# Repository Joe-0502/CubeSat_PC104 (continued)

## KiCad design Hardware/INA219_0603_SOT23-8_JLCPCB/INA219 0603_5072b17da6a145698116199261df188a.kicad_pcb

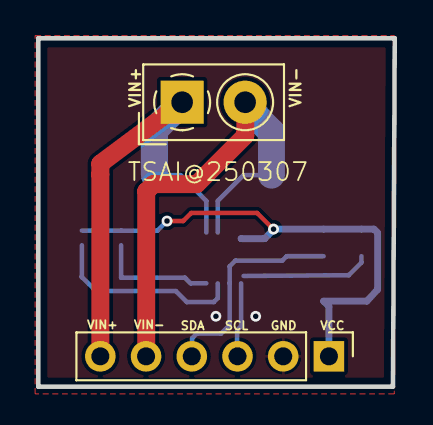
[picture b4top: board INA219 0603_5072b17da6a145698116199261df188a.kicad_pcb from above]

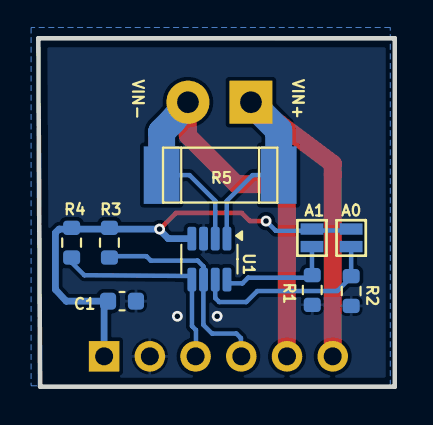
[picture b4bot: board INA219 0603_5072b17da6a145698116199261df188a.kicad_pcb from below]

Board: 2 copper layers, 19.8 x 19.4 mm, 11 parts (9 on the bottom side), 8 nets.

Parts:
C1: 100nF; C_0603_1608Metric
J1: Conn_01x06; PinHeader_1x06_P2.54mm_Vertical
JP1: M023.5MM; TerminalBlock_4Ucon_1x02_P3.50mm_Horizontal_small
R1, R2, R3, R4: 10K; R_0603_1608Metric
R5: 0.1; R_2512
SJ1, SJ2: SOLDERJUMPERNC_TR; SolderJumper_2
U1: INA219AIDCNR; SOT-23-8

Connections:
GND: C1.1, J1.2, R1.2, R2.2, U1.3 (GND)
unnamed: R2.1, SJ2.1, U1.7 (A0)
unnamed: R1.1, SJ1.1, U1.8 (A1)
SCL: J1.3, R4.1, U1.5 (SCL)
SDA: J1.4, R3.1, U1.6 (SDA)
VCC: C1.2, J1.1, R3.2, R4.2, SJ1.2, SJ2.2, U1.4 (VS)
VIN+: J1.6, JP1.1, R5.1, U1.1 (IN+)
VIN-: J1.5, JP1.2, R5.2, U1.2 (IN-)

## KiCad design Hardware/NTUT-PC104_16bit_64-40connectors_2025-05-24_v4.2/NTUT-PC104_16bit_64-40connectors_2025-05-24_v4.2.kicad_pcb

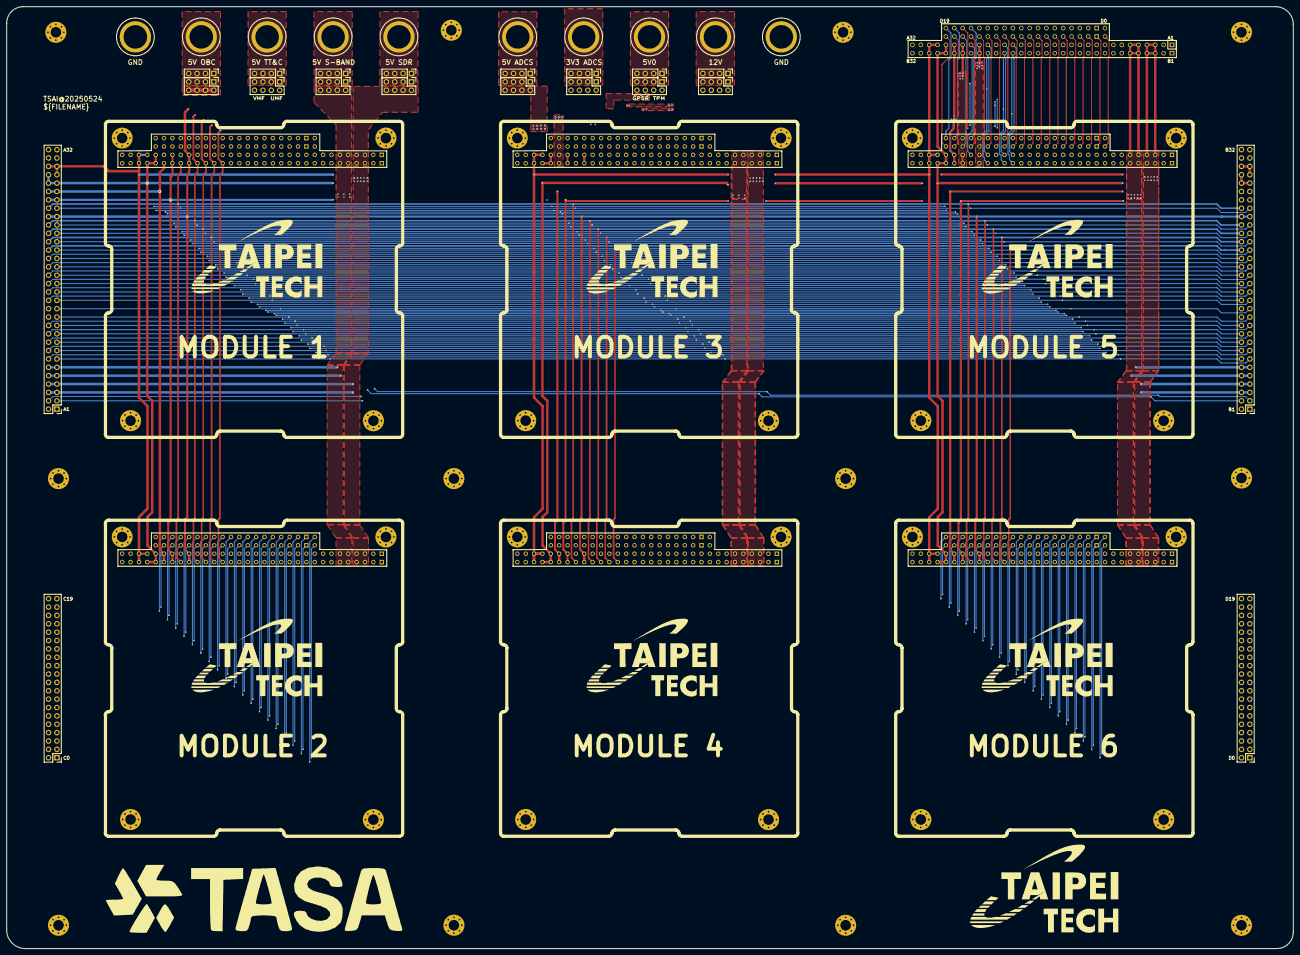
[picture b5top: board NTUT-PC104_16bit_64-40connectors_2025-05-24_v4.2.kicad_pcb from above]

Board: 4 copper layers, 390.3 x 285.7 mm, 49 parts (0 on the bottom side), 92 nets.

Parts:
H1, H2, H3, H4, H5, H6, H7, H8, H9, H10, H11, H12: MountingHole_Pad; MountingHole_3.2mm_M3_Pad_Via
J1, J2, J3, J4, J5, J6: CubeSat_PC104_16bit_footprint
J7, J12, J13, J14, J15, J16, J17, J18: Conn_02x04_Odd_Even; PinHeader_2x04_P2.54mm_Vertical
J8, J10: Conn_02x26_Odd_Even; PinHeader_2x20_P2.54mm_Vertical
J9: Conn_02x26_Odd_Even; PinHeader_2x32_P2.54mm_Vertical
J11: PC104_16bit_Connector
J19, J20, J21, J22, J23, J24, J25, J26: Conn_01x04; PinHeader_1x04_P2.54mm_Vertical
JA19: Conn_02x26_Odd_Even; PinHeader_2x32_P2.54mm_Vertical
TP1, TP2, TP3, TP4, TP5, TP6, TP7, TP8, TP9, TP10: TestPoint_Alt; KSE_PN6095

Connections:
/3.3V_ADCS_1W: J1.B22, J2.B22, J3.B22, J4.B22, J5.B22, J6.B22, J9.44, J11.B22, J16.2, J16.4, J16.6, J16.8, JA19.44
/3V3_ADCS: J16.1, J16.3, J16.5, J16.7, J24.1, J24.2, J24.3, J24.4, TP7.1
/5V: J18.1, J18.3, J18.5, J18.7, J26.1, J26.2, J26.3, J26.4, TP9.1
/5V_ADCS: J15.1, J15.3, J15.5, J15.7, J23.1, J23.2, J23.3, J23.4, TP6.1
/5V_ADCS_1.2W: J1.B23, J2.B23, J3.B23, J4.B23, J5.B23, J6.B23, J9.46, J11.B23, J15.2, J15.4, J15.6, J15.8, JA19.46
/5V_GPSR_0.6W: J1.B21, J2.B21, J3.B21, J4.B21, J5.B21, J6.B21, J9.42, J11.B21, J18.6, J18.8, JA19.42
/5V_OBC: J14.1, J14.3, J14.5, J14.7, J22.1, J22.2, J22.3, J22.4, TP4.1
/5V_OBC_5W: J1.A27, J1.B27, J2.A27, J2.B27, J3.A27, J3.B27, J4.A27, J4.B27, J5.A27, J5.B27, J6.A27, J6.B27, J9.53, J9.54, J11.A27, J11.B27, J14.2, J14.4, J14.6, J14.8, JA19.53, JA19.54
/5V_S-BAND: J12.1, J12.3, J12.5, J12.7, J20.1, J20.2, J20.3, J20.4, TP2.1
/5V_S-BAND_12W: J1.A5, J1.A6, J1.B5, J1.B6, J2.A5, J2.A6, J2.B5, J2.B6, J3.A5, J3.A6, J3.B5, J3.B6, J4.A5, J4.A6, J4.B5, J4.B6, J5.A5, J5.A6, J5.B5, J5.B6, J6.A5, J6.A6, J6.B5, J6.B6, J9.9, J9.10, J9.11, J9.12, J11.A5, J11.A6, J11.B5, J11.B6, J12.2, J12.4, J12.6, J12.8, JA19.9, JA19.10, JA19.11, JA19.12
/5V_SDR: J7.1, J7.3, J7.5, J7.7, J19.1, J19.2, J19.3, J19.4, TP1.1
/5V_SDR_10W: J1.A3, J1.A4, J1.B3, J1.B4, J2.A3, J2.A4, J2.B3, J2.B4, J3.A3, J3.A4, J3.B3, J3.B4, J4.A3, J4.A4, J4.B3, J4.B4, J5.A3, J5.A4, J5.B3, J5.B4, J6.A3, J6.A4, J6.B3, J6.B4, J7.2, J7.4, J7.6, J7.8, J9.5, J9.6, J9.7, J9.8, J11.A3, J11.A4, J11.B3, J11.B4, JA19.5, JA19.6, JA19.7, JA19.8
/5V_TPM_0.4W: J1.B20, J2.B20, J3.B20, J4.B20, J5.B20, J6.B20, J9.40, J11.B20, J18.2, J18.4, JA19.40
/5V_TT&C: J13.1, J13.3, J13.5, J13.7, J21.1, J21.2, J21.3, J21.4, TP3.1
/5V_TT&C(UHF)_3.5W: J1.A24, J1.B24, J2.A24, J2.B24, J3.A24, J3.B24, J4.A24, J4.B24, J5.A24, J5.B24, J6.A24, J6.B24, J9.47, J9.48, J11.A24, J11.B24, J13.2, J13.4, JA19.47, JA19.48
/5V_TT&C(VHF)_3.5W: J1.A26, J1.B26, J2.A26, J2.B26, J3.A26, J3.B26, J4.A26, J4.B26, J5.A26, J5.B26, J6.A26, J6.B26, J9.51, J9.52, J11.A26, J11.B26, J13.6, J13.8, JA19.51, JA19.52
/12V: J17.1, J17.3, J17.5, J17.7, J25.1, J25.2, J25.3, J25.4, TP8.1
/+5V: J1.B25, J2.B25, J3.B25, J4.B25, J5.B25, J6.B25, J9.50, J11.B25, JA19.50
/ADSBRX: J1.A23, J2.A23, J3.A23, J4.A23, J5.A23, J6.A23, J9.45, J11.A23, JA19.45
/ADSBTX: J1.A22, J2.A22, J3.A22, J4.A22, J5.A22, J6.A22, J9.43, J11.A22, JA19.43
/BAT_I_AD: J1.B8, J2.B8, J3.B8, J4.B8, J5.B8, J6.B8, J9.16, J11.B8, JA19.16
/C0: J1.C0, J2.C0, J3.C0, J4.C0, J5.C0, J6.C0, J8.1, J10.1, J11.C0
/C1: J1.C1, J2.C1, J3.C1, J4.C1, J5.C1, J6.C1, J8.3, J10.3, J11.C1
/C2: J1.C2, J2.C2, J3.C2, J4.C2, J5.C2, J6.C2, J8.5, J10.5, J11.C2
/C3: J1.C3, J2.C3, J3.C3, J4.C3, J5.C3, J6.C3, J8.7, J10.7, J11.C3
/C4: J1.C4, J2.C4, J3.C4, J4.C4, J5.C4, J6.C4, J8.9, J10.9, J11.C4
/C5: J1.C5, J2.C5, J3.C5, J4.C5, J5.C5, J6.C5, J8.11, J10.11, J11.C5
/C6: J1.C6, J2.C6, J3.C6, J4.C6, J5.C6, J6.C6, J8.13, J10.13, J11.C6
/C7: J1.C7, J2.C7, J3.C7, J4.C7, J5.C7, J6.C7, J8.15, J10.15, J11.C7
/C8: J1.C8, J2.C8, J3.C8, J4.C8, J5.C8, J6.C8, J8.17, J10.17, J11.C8
/C9: J1.C9, J2.C9, J3.C9, J4.C9, J5.C9, J6.C9, J8.19, J10.19, J11.C9
/C10: J1.C10, J2.C10, J3.C10, J4.C10, J5.C10, J6.C10, J8.21, J10.21, J11.C10
/C11: J1.C11, J2.C11, J3.C11, J4.C11, J5.C11, J6.C11, J8.23, J10.23, J11.C11
/C12: J1.C12, J2.C12, J3.C12, J4.C12, J5.C12, J6.C12, J8.25, J10.25, J11.C12
/C13: J1.C13, J2.C13, J3.C13, J4.C13, J5.C13, J6.C13, J8.27, J10.27, J11.C13
/C14: J1.C14, J2.C14, J3.C14, J4.C14, J5.C14, J6.C14, J8.29, J10.29, J11.C14
/C15: J1.C15, J2.C15, J3.C15, J4.C15, J5.C15, J6.C15, J8.31, J10.31, J11.C15
/C16: J1.C16, J2.C16, J3.C16, J4.C16, J5.C16, J6.C16, J8.33, J10.33, J11.C16
/C17: J1.C17, J2.C17, J3.C17, J4.C17, J5.C17, J6.C17, J8.35, J10.35, J11.C17
/C18: J1.C18, J2.C18, J3.C18, J4.C18, J5.C18, J6.C18, J8.37, J10.37, J11.C18
/C19: J1.C19, J2.C19, J3.C19, J4.C19, J5.C19, J6.C19, J8.39, J10.39, J11.C19
/D0: J1.D0, J2.D0, J3.D0, J4.D0, J5.D0, J6.D0, J8.2, J10.2, J11.D0
/D1: J1.D1, J2.D1, J3.D1, J4.D1, J5.D1, J6.D1, J8.4, J10.4, J11.D1
/D2: J1.D2, J2.D2, J3.D2, J4.D2, J5.D2, J6.D2, J8.6, J10.6, J11.D2
/D3: J1.D3, J2.D3, J3.D3, J4.D3, J5.D3, J6.D3, J8.8, J10.8, J11.D3
/D4: J1.D4, J2.D4, J3.D4, J4.D4, J5.D4, J6.D4, J8.10, J10.10, J11.D4
/D5: J1.D5, J2.D5, J3.D5, J4.D5, J5.D5, J6.D5, J8.12, J10.12, J11.D5
/D6: J1.D6, J2.D6, J3.D6, J4.D6, J5.D6, J6.D6, J8.14, J10.14, J11.D6
/D7: J1.D7, J2.D7, J3.D7, J4.D7, J5.D7, J6.D7, J8.16, J10.16, J11.D7
/D8: J1.D8, J2.D8, J3.D8, J4.D8, J5.D8, J6.D8, J8.18, J10.18, J11.D8
/D9: J1.D9, J2.D9, J3.D9, J4.D9, J5.D9, J6.D9, J8.20, J10.20, J11.D9
/D10: J1.D10, J2.D10, J3.D10, J4.D10, J5.D10, J6.D10, J8.22, J10.22, J11.D10
/D11: J1.D11, J2.D11, J3.D11, J4.D11, J5.D11, J6.D11, J8.24, J10.24, J11.D11
/D12: J1.D12, J2.D12, J3.D12, J4.D12, J5.D12, J6.D12, J8.26, J10.26, J11.D12
/D13: J1.D13, J2.D13, J3.D13, J4.D13, J5.D13, J6.D13, J8.28, J10.28, J11.D13
/D14: J1.D14, J2.D14, J3.D14, J4.D14, J5.D14, J6.D14, J8.30, J10.30, J11.D14
/D15: J1.D15, J2.D15, J3.D15, J4.D15, J5.D15, J6.D15, J8.32, J10.32, J11.D15
/D16: J1.D16, J2.D16, J3.D16, J4.D16, J5.D16, J6.D16, J8.34, J10.34, J11.D16
/D17: J1.D17, J2.D17, J3.D17, J4.D17, J5.D17, J6.D17, J8.36, J10.36, J11.D17
/D18: J1.D18, J2.D18, J3.D18, J4.D18, J5.D18, J6.D18, J8.38, J10.38, J11.D18
/D19: J1.D19, J2.D19, J3.D19, J4.D19, J5.D19, J6.D19, J8.40, J10.40, J11.D19
/DC_BUS: J1.A29, J1.A30, J1.B30, J2.A29, J2.A30, J2.B30, J3.A29, J3.A30, J3.B30, J4.A29, J4.A30, J4.B30, J5.A29, J5.A30, J5.B30, J6.A29, J6.A30, J6.B30, J9.57, J9.59, J9.60, J11.A29, J11.A30, J11.B30, JA19.57, JA19.59, JA19.60
/DC_BUS_1: J1.A28, J1.B28, J1.B29, J2.A28, J2.B28, J2.B29, J3.A28, J3.B28, J3.B29, J4.A28, J4.B28, J4.B29, J5.A28, J5.B28, J5.B29, J6.A28, J6.B28, J6.B29, J9.55, J9.56, J9.58, J11.A28, J11.B28, J11.B29, JA19.55, JA19.56, JA19.58
/EPS_RX: J1.A8, J2.A8, J3.A8, J4.A8, J5.A8, J6.A8, J9.15, J11.A8, JA19.15
/EPS_TX: J1.A9, J2.A9, J3.A9, J4.A9, J5.A9, J6.A9, J9.17, J11.A9, JA19.17
/GPS_RX: J1.A15, J2.A15, J3.A15, J4.A15, J5.A15, J6.A15, J9.29, J11.A15, JA19.29
/GPS_TX: J1.A14, J2.A14, J3.A14, J4.A14, J5.A14, J6.A14, J9.27, J11.A14, JA19.27
/NULL1: J1.A2, J2.A2, J3.A2, J4.A2, J5.A2, J6.A2, J9.3, J11.A2, JA19.3
/NULL2: J1.A7, J2.A7, J3.A7, J4.A7, J5.A7, J6.A7, J9.13, J11.A7, JA19.13
/NULL3: J1.A25, J2.A25, J3.A25, J4.A25, J5.A25, J6.A25, J9.49, J11.A25, JA19.49
/NULL4: J1.B7, J2.B7, J3.B7, J4.B7, J5.B7, J6.B7, J9.14, J11.B7, JA19.14
/NULL5: J1.B18, J2.B18, J3.B18, J4.B18, J5.B18, J6.B18, J9.36, J11.B18, JA19.36
/NULL6: J1.B19, J2.B19, J3.B19, J4.B19, J5.B19, J6.B19, J9.38, J11.B19, JA19.38
/OBC1: J1.B15, J2.B15, J3.B15, J4.B15, J5.B15, J6.B15, J9.30, J11.B15, JA19.30
/OBC2: J1.B16, J2.B16, J3.B16, J4.B16, J5.B16, J6.B16, J9.32, J11.B16, JA19.32
/OBC3: J1.B17, J2.B17, J3.B17, J4.B17, J5.B17, J6.B17, J9.34, J11.B17, JA19.34
/OUTPW1: J1.A21, J2.A21, J3.A21, J4.A21, J5.A21, J6.A21, J9.41, J11.A21, JA19.41
/OUTPW1_1: J1.B11, J2.B11, J3.B11, J4.B11, J5.B11, J6.B11, J9.22, J11.B11, JA19.22
/OUTPW2: J1.A20, J2.A20, J3.A20, J4.A20, J5.A20, J6.A20, J9.39, J11.A20, JA19.39
/OUTPW3: J1.A19, J2.A19, J3.A19, J4.A19, J5.A19, J6.A19, J9.37, J11.A19, JA19.37
/OUTPW4: J1.A18, J2.A18, J3.A18, J4.A18, J5.A18, J6.A18, J9.35, J11.A18, JA19.35
/OUTPW5: J1.A17, J2.A17, J3.A17, J4.A17, J5.A17, J6.A17, J9.33, J11.A17, JA19.33
/OUTPW6: J1.A16, J2.A16, J3.A16, J4.A16, J5.A16, J6.A16, J9.31, J11.A16, JA19.31
/PPS: J1.B14, J2.B14, J3.B14, J4.B14, J5.B14, J6.B14, J9.28, J11.B14, JA19.28
/RESET1: J1.B2, J2.B2, J3.B2, J4.B2, J5.B2, J6.B2, J9.4, J11.B2, JA19.4
/S_Band/CS04: J1.A13, J2.A13, J3.A13, J4.A13, J5.A13, J6.A13, J9.25, J11.A13, JA19.25
/S_Band/SPIMISO: J1.A12, J2.A12, J3.A12, J4.A12, J5.A12, J6.A12, J9.23, J11.A12, JA19.23
/S_Band/SPIMOSI: J1.A11, J2.A11, J3.A11, J4.A11, J5.A11, J6.A11, J9.21, J11.A11, JA19.21
/S_Band/SPI_INT_SCK: J1.A10, J2.A10, J3.A10, J4.A10, J5.A10, J6.A10, J9.19, J11.A10, JA19.19
/T_BAT: J1.B10, J2.B10, J3.B10, J4.B10, J5.B10, J6.B10, J9.20, J11.B10, JA19.20
/T_ENV: J1.B9, J2.B9, J3.B9, J4.B9, J5.B9, J6.B9, J9.18, J11.B9, JA19.18
GND: H1.1, H2.1, H3.1, H4.1, H5.1, H6.1, H7.1, H8.1, H9.1, H10.1, H11.1, H12.1, J1.A1, J1.A31, J1.A32, J1.B1, J1.B12, J1.B13, J1.B31, J1.B32, J2.A1, J2.A31, J2.A32, J2.B1, J2.B12, J2.B13, J2.B31, J2.B32, J3.A1, J3.A31, J3.A32, J3.B1, J3.B12, J3.B13, J3.B31, J3.B32, J4.A1, J4.A31, J4.A32, J4.B1, J4.B12, J4.B13, J4.B31, J4.B32, J5.A1, J5.A31, J5.A32, J5.B1, J5.B12, J5.B13, J5.B31, J5.B32, J6.A1, J6.A31, J6.A32, J6.B1, J6.B12, J6.B13, J6.B31, J6.B32, J9.1, J9.2, J9.24, J9.26, J9.61, J9.62, J9.63, J9.64, J11.A1, J11.A31, J11.A32, J11.B1, J11.B12, J11.B13, J11.B31, J11.B32, JA19.1, JA19.2, JA19.24, JA19.26, JA19.61, JA19.62, JA19.63, JA19.64, TP5.1, TP10.1
